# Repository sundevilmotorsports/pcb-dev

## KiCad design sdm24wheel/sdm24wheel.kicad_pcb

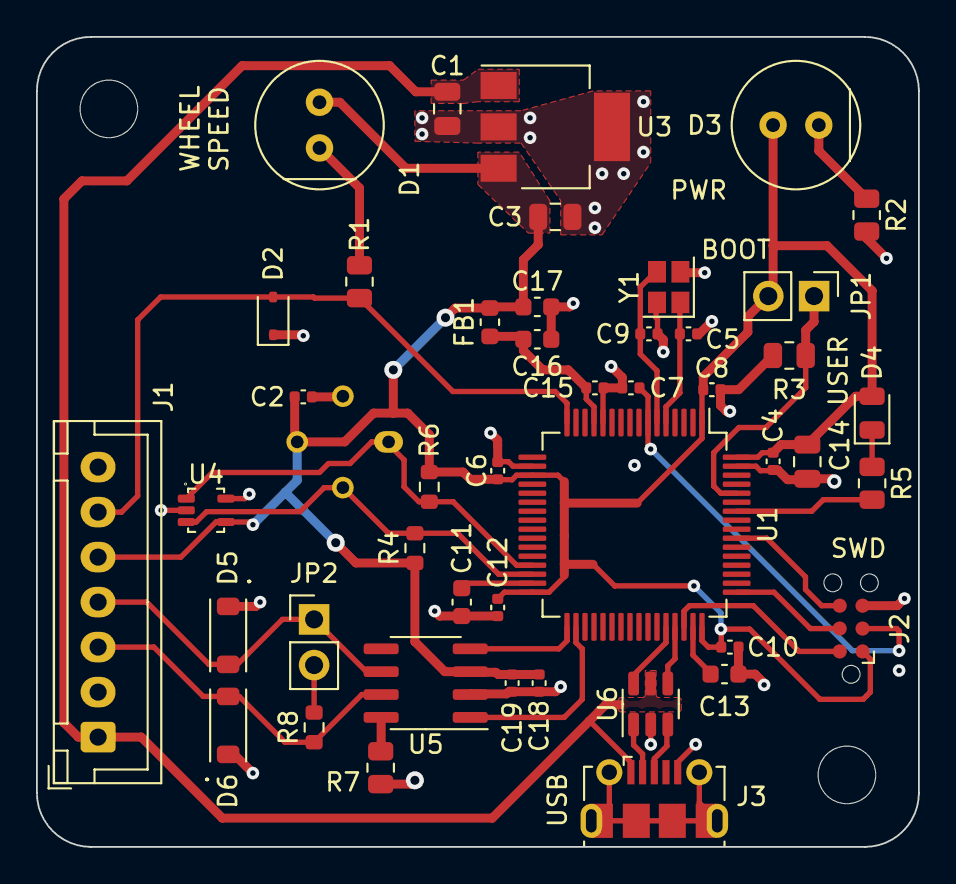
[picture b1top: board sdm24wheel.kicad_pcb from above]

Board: 4 copper layers, 49.0 x 45.0 mm, 48 parts (1 on the bottom side), 30 nets.

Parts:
C1, C3, C14: 10uF; C_0805_2012Metric
C2, C4, C6, C7, C8, C10, C12, C15, C18, C19: 100nF; C_0402_1005Metric
C5, C9: 10pF; C_0402_1005Metric
C11, C13: 2.2uF; C_0603_1608Metric
C16, C17: 1uF; C_0603_1608Metric
D1: GREEN; Dialight_561-XX0X-XXX
D2: TVS; D_SOD-323
D3: RED; Dialight_561-XX0X-XXX
D4: GREEN; LED_0805_2012Metric
D5, D6: TVS; SOD-123FL
FB1: 120R; L_0603_1608Metric
H1, H2: M3; MountingHole_3.2mm_M3
J1: JST-XH; JST_XH_B7B-XH-A_1x07_P2.50mm_Vertical
J2: Conn_ARM_SWD_TagConnect_TC2030; Tag-Connect_TC2030-IDC-NL_2x03_P1.27mm_Vertical
J3: USB_B_Micro; USB_Micro-B_Molex-105017-0001
JP1: BOOT; PinHeader_1x02_P2.54mm_Vertical
JP2: Bus Termination; PinHeader_1x02_P2.54mm_Vertical
R1, R2, R5: 220; R_0805_2012Metric
R3, R7: 10k; R_0805_2012Metric
R4, R6: 2.7k; R_0603_1608Metric
R8: 120; R_0603_1608Metric
U1: STM32F405RGT6; LQFP-64_10x10mm_P0.5mm
U2: MLX90614; TO-39-4
U3: MIC37100-3.3WS; SOT-223-3_TabPin2
U4: 24LC01BT-E/LT; SC-70-5
U5: SN65HVD230; SOIC-8_3.9x4.9mm_P1.27mm
U6: USBLC6-2SC6; SOT-23-6
Y1: 12MHz; Crystal_SMD_2520-4Pin_2.5x2.0mm

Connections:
+3.3V: C2.1, C3.1, C4.1, C6.1, C8.1, C10.1, C12.1, C14.1, C17.1, C18.1, C19.1, D1.2 (A), D3.2 (A), D4.2 (A), FB1.2, J1.5, J2.1 (VCC), JP1.2 (B), R4.1, R6.1, U1.1 (VBAT), U1.19 (VDD), U1.32 (VDD), U1.48 (VDD), U1.64 (VDD), U2.3 (VDD), U3.3 (OUT), U4.4 (Vcc), U5.3 (VCC)
+3.3VA: C15.1, C16.1, FB1.1, U1.13 (VDDA)
/BOOT0: JP1.1 (A), R3.2, U1.60 (BOOT0)
/CAN+: D6.2 (A2), J1.3, R8.1, U5.7 (CANH)
/CAN-: D5.2 (A2), J1.4, JP2.1 (A), U5.6 (CANL)
/CAN_Rs: R7.1, U5.8 (Rs)
/CRX: U1.33 (PB12), U5.4 (R)
/CTX: U1.34 (PB13), U5.1 (D)
/HE_LED: D1.1 (K), R1.2
/HE_OUTPUT: D2.2 (A2), J1.6, R1.1, U1.16 (PA2)
/HSE_IN: C5.1, U1.5 (PH0), Y1.1
/HSE_OUT: C9.1, U1.6 (PH1), Y1.3
/I2C2_SCL: R6.2, U1.29 (PB10), U2.1 (SCL), U4.1 (SCL)
/I2C2_SDA: R4.2, U1.30 (PB11), U2.2 (SDA), U4.3 (SDA)
/NRST: C7.1, J2.3 (~RESET), U1.7 (NRST)
/PWR_LED: D3.1 (K), R2.1
/SWCLK: J2.4 (SWCLK), U1.49 (PA14)
/SWDIO: J2.2 (SWDIO), U1.46 (PA13)
/SWO: J2.6 (SWO), U1.55 (PB3)
/USB_D+: U1.45 (PA12), U6.4 (I/O2)
/USB_D-: U1.44 (PA11), U6.6 (I/O1)
/USB_J_D+: J3.3 (D+), U6.3 (I/O2)
/USB_J_D-: J3.2 (D-), U6.1 (I/O1)
/USER_LED: R5.2, U1.58 (PB6)
/VCAP1: C11.1, U1.31 (VCAP_1)
/VCAP2: C13.1, U1.47 (VCAP_2)
GND: C1.2, C2.2, C3.2, C4.2, C5.2, C6.2, C7.2, C8.2, C9.2, C10.2, C11.2, C12.2, C13.2, C14.2, C15.2, C16.2, C17.2, C18.2, C19.2, D2.1 (A1), D5.1 (A1), D6.1 (A1), J1.2, J1.7, J2.5 (GND), J3.5 (GND), R2.2, R3.1, R7.2, U1.12 (VSSA), U1.18 (VSS), U1.63 (VSS), U2.4 (GND), U3.2 (GND), U4.2 (Vss), U4.5 (WP), U5.2 (GND), U6.2 (GND), Y1.2, Y1.4
unnamed: D4.1 (K), R5.1
unnamed: JP2.2 (B), R8.2
VCC: C1.1, J1.1, J3.1 (VBUS), U3.1 (IN), U6.5 (VBUS)

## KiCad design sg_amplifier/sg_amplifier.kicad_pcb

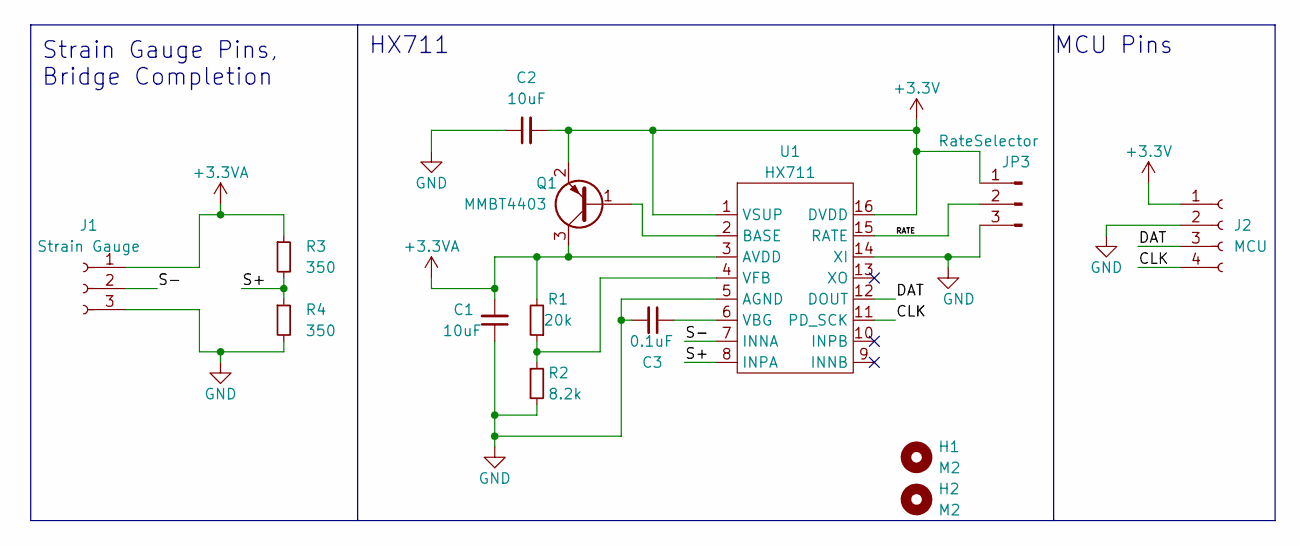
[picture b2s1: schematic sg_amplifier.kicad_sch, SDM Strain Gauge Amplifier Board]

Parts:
C1, C2: 10uF; C_0603_1608Metric
C3: 0.1uF; C_0402_1005Metric
H1, H2: M2; MountingHole_2.2mm_M2
J1: Strain Gauge; TerminalBlock_TE_282834-3_1x03_P2.54mm_Horizontal
J2: MCU; TerminalBlock_TE_282834-4_1x04_P2.54mm_Horizontal
JP3: RateSelector; PinHeader_1x03_P2.54mm_Vertical
Q1: MMBT4403; SOT-23
R1: 20k; R_0805_2012Metric
R2: 8.2k; R_0402_1005Metric
R3, R4: 350; R_Axial_DIN0414_L11.9mm_D4.5mm_P15.24mm_Horizontal
U1: HX711; SOP-16_3.9x9.9mm_P1.27mm

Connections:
+3.3V: C2.2, J2.1, JP3.1, Q1.2 (E), U1.1 (VSUP), U1.16 (DVDD)
+3.3VA: C1.2, J1.1, Q1.3 (C), R1.2, R3.1, U1.3 (AVDD)
/CLK: J2.4, U1.11 (PD_SCK)
/DAT: J2.3, U1.12 (DOUT)
/RATE: JP3.2, U1.15 (RATE)
/S+: R3.2, R4.1, U1.8 (INPA)
/S-: J1.2, U1.7 (INNA)
GND: C1.1, C2.1, C3.2, J1.3, J2.2, JP3.3, R2.2, R4.2, U1.5 (AGND), U1.14 (XI)
unnamed: C3.1, U1.6 (VBG)
unnamed: Q1.1 (B), U1.2 (BASE)
unnamed: R1.1, R2.1, U1.4 (VFB)

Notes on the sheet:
MCU Pins
Strain Gauge Pins, Bridge Completion
HX711

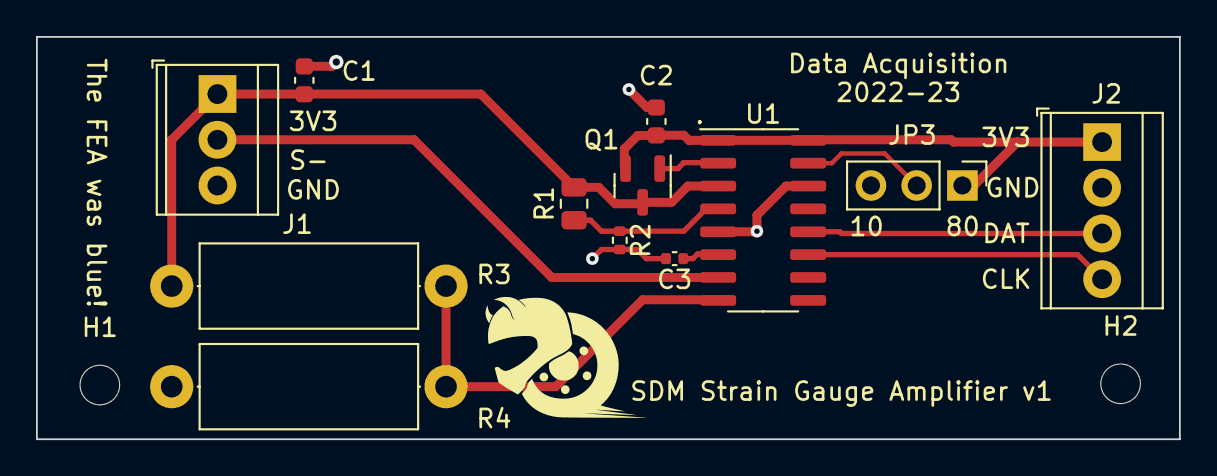
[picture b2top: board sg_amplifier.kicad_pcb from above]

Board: 2 copper layers, 63.5 x 22.4 mm, 14 parts (0 on the bottom side), 11 nets.

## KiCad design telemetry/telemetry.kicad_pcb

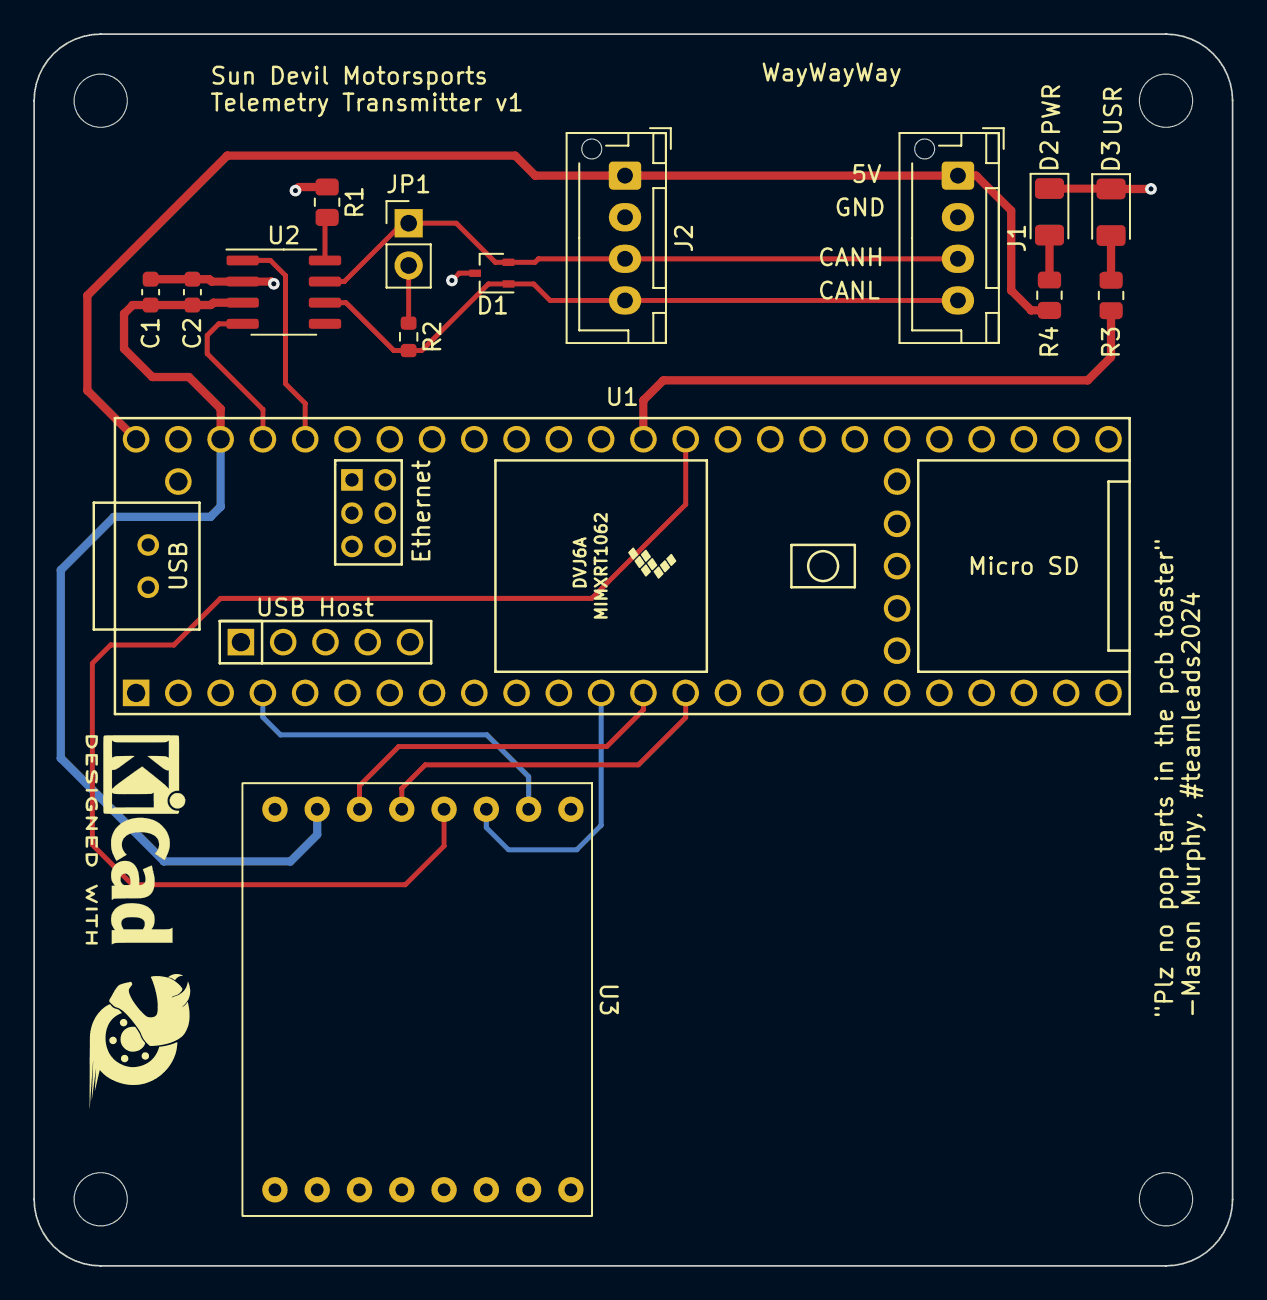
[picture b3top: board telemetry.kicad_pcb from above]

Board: 2 copper layers, 72.0 x 74.0 mm, 19 parts (0 on the bottom side), 17 nets.

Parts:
C1, C2: 100nF; C_0603_1608Metric
D1: ESDCAN; SOT-323_SC-70
D2: RED; LED_1206_3216Metric
D3: GREEN; LED_1206_3216Metric
H1, H2, H3, H4: M3; MountingHole_3.2mm_M3
J1: CAN; JST_XH_B4B-XH-AM_1x04_P2.50mm_Vertical
J2: CAN_DaisyChain; JST_XH_B4B-XH-AM_1x04_P2.50mm_Vertical
JP1: Bus Termination; PinHeader_1x02_P2.54mm_Vertical
R1: 10k; R_0805_2012Metric
R2: 120; R_0603_1608Metric
R3: 500; R_0805_2012Metric
R4: 220; R_0805_2012Metric
U1: Teensy4.1; Teensy41
U2: SN65HVD230; SOIC-8_3.9x4.9mm_P1.27mm
U3: nrf24L01-click

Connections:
+3.3V: C1.1, C2.1, U1.46 (3V3), U2.3 (VCC), U3.7 (3V3)
+5V: J1.1, J2.1, R4.1, U1.48 (VIN)
/CANH: D1.2 (A2), J1.3, J2.3, JP1.1 (A), U2.7 (CANH)
/CANL: D1.1 (A1), J1.4, J2.4, R2.2, U2.6 (CANL)
/CAN_Rs: R1.2, U2.8 (Rs)
/CE: U1.4 (2_OUT2), U3.2 (CE)
/CRX1: U1.45 (23_A9_CRX1_MCLK1), U2.4 (R)
/CS: U1.12 (10_CS_MQSR), U3.3 (CS)
/CTX1: U1.44 (22_A8_CTX1), U2.1 (D)
/MISO: U1.14 (12_MISO_MQSL), U3.5 (SDO)
/MOSI: U1.13 (11_MOSI_CTX1), U3.6 (SDI)
/PWR_LED: D2.2 (A), R4.2
/SCK: U1.35 (13_SCK_LED), U3.4 (SCK)
/USER_LED: R3.1, U1.36 (14_A0_TX3_SPDIF_OUT)
/USR_LED_RSTR: D3.2 (A), R3.2
GND: C1.2, C2.2, D1.3 (common), D2.1 (K), D3.1 (K), J1.2, J2.2, R1.1, U1.1 (GND), U1.34 (GND), U1.47 (GND), U2.2 (GND), U3.8 (GND), U3.9 (GND)
unnamed: JP1.2 (B), R2.1

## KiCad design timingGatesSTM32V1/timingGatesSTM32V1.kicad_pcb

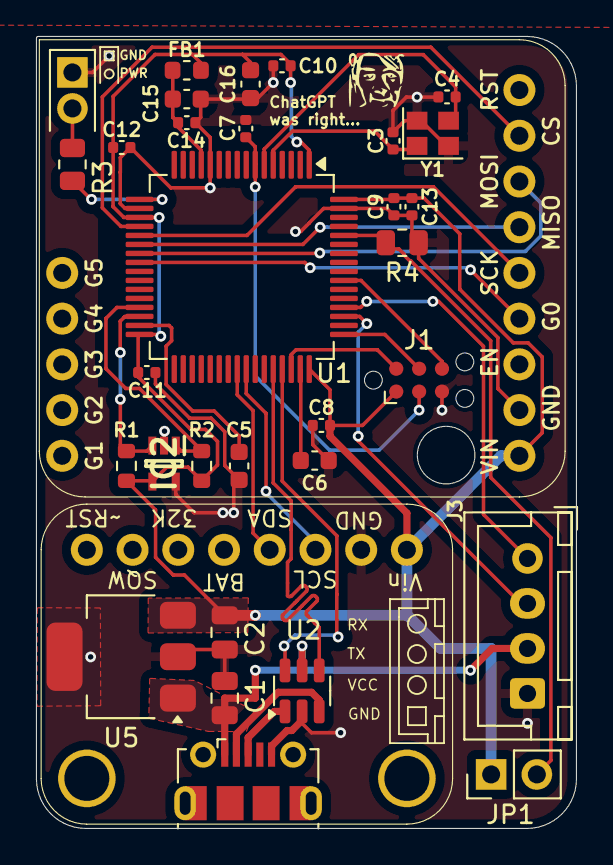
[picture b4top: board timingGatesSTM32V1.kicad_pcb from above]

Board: 4 copper layers, 30.0 x 44.0 mm, 34 parts (0 on the bottom side), 30 nets.

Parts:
C1, C2: 10uF; C_0805_2012Metric
C3, C4: 10pF; C_0402_1005Metric
C5, C6: 2.2uF; C_0603_1608Metric
C7, C8, C9, C10, C11, C12, C13, C14: 100nF; C_0402_1005Metric
C15, C16: 1uF; C_0603_1608Metric
D1: RED (floating); LED_0805_2012Metric
FB1: 120R; L_0603_1608Metric
H1: M3; MountingHole_3.2mm_M3
IC2: 24LC01BT-E_LT; SOT65P210X110-5N
J1: Conn_ARM_SWD_TagConnect_TC2030; Tag-Connect_TC2030-IDC-NL_2x03_P1.27mm_Vertical
J2: USB_B_Micro; USB_Micro-B_Molex-105017-0001
J3: Conn_01x04_Socket; JST_XH_B4B-XH-A_1x04_P2.50mm_Vertical
JP1: BOOT; PinHeader_1x02_P2.54mm_Vertical
R1, R2: 2.7k; R_0603_1608Metric
R3: 220; R_0805_2012Metric
R4: 10k; R_0805_2012Metric
U1: STM32F405RGT6; LQFP-64_10x10mm_P0.5mm
U2: USBLC6-2SC6; SOT-23-6
U3: RFM95W
U4: DS3231
U5: MIC37100-3.3WS; SOT-223-3_TabPin2
Y1: 12MHz; Crystal_SMD_2520-4Pin_2.5x2.0mm

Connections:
+3.3V: C2.1, C8.2, C9.2, C10.2, C11.2, C12.2, C13.2, C16.2, FB1.2, IC2.4 (VCC), J1.1 (VCC), JP1.1 (A), R1.2, R2.2, U1.1 (VBAT), U1.19 (VDD), U1.32 (VDD), U1.48 (VDD), U1.64 (VDD), U3.1 (Vin), U4.1 (Vin), U5.3 (OUT)
/BOOT0: JP1.2 (B), R4.2, U1.60 (BOOT0)
/G0: U1.24 (PC4), U3.4 (G0)
/HSE_IN: C3.1, U1.5 (PH0), Y1.1
/HSE_OUT: C4.1, U1.6 (PH1), Y1.3
/I2C2_SCL: IC2.1 (SCL), R2.1, U1.29 (PB10)
/I2C2_SDA: IC2.3 (SDA), R1.1, U1.30 (PB11)
/I2C3_SCL: U1.41 (PA8), U4.3 (SCL)
/I2C3_SDA: U1.40 (PC9), U4.4 (SDA)
/NRST: C7.2, J1.3 (~RESET), U1.7 (NRST)
/SPI1_MISO: U1.22 (PA6), U3.6 (MISO)
/SPI1_MOSI: U1.23 (PA7), U3.7 (MOSI)
/SPI1_NSS: U1.20 (PA4), U3.8 (CS)
/SPI1_SCK: U1.21 (PA5), U3.5 (SCK)
/SWCLK: J1.4 (SWCLK), U1.49 (PA14)
/SWDIO: J1.2 (SWDIO), U1.46 (PA13)
/SWO: J1.6 (SWO), U1.55 (PB3)
/USART3_RX: J3.1, U1.52 (PC11)
/USART3_TX: J3.2, U1.51 (PC10)
/USB_D+: U1.45 (PA12), U2.6 (I/O1)
/USB_D-: U1.44 (PA11), U2.4 (I/O2)
/VCAP_1: C5.1, U1.31 (VCAP_1)
/VCAP_2: C6.2, U1.47 (VCAP_2)
GND: C1.2, C2.2, C3.2, C4.2, C5.2, C6.1, C7.1, C8.1, C9.1, C10.1, C11.1, C12.1, C13.1, C14.1, C15.1, C16.1, D1.1 (K), IC2.2 (Vss), IC2.5 (WP), J1.5 (GND), J2.5 (GND), J3.4, R4.1, U1.12 (VSSA), U1.18 (VSS), U1.63 (VSS), U2.2 (GND), U3.2 (GND), U4.2 (GND), U5.2 (GND), Y1.2, Y1.4
unnamed: D1.2 (A), R3.1
unnamed: J2.3 (D+), U2.1 (I/O1)
unnamed: J2.2 (D-), U2.3 (I/O2)
unnamed: R3.2, U1.17 (PA3)
unnamed: C14.2, C15.2, FB1.1, U1.13 (VDDA)
VCC: C1.1, J2.1 (VBUS), J3.3, U2.5 (VBUS), U5.1 (IN)

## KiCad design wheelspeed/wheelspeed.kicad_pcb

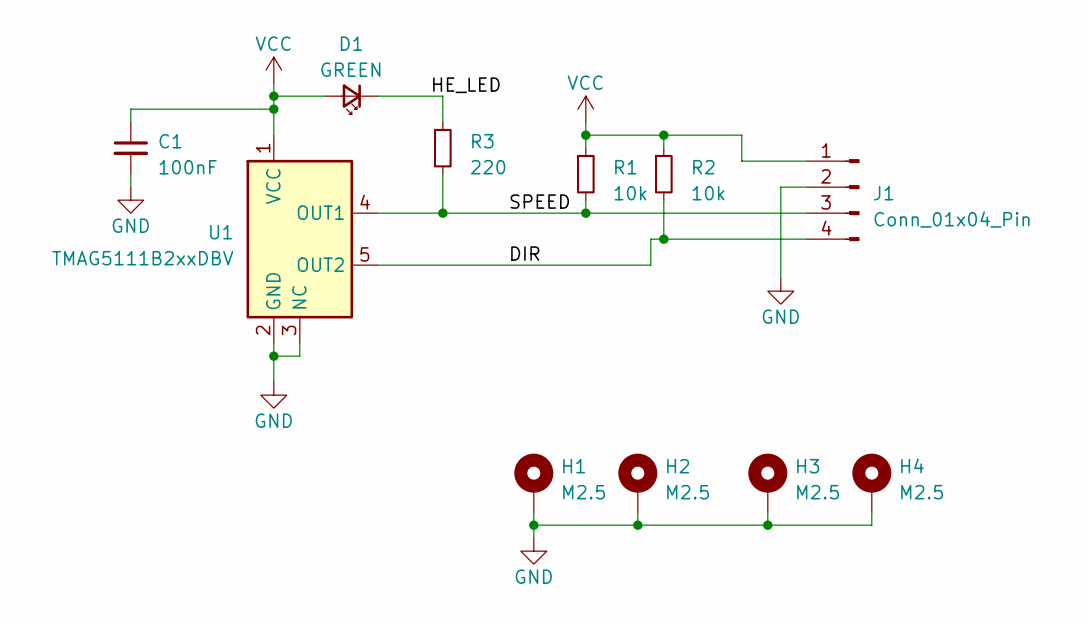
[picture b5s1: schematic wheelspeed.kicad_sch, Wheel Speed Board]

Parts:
C1: 100nF; C_0603_1608Metric
D1: GREEN; LED_1206_3216Metric
H1, H2, H3, H4: M2.5; MountingHole_2.7mm_M2.5_ISO7380_Pad
J1: Conn_01x04_Pin; JST_XH_B4B-XH-AM_1x04_P2.50mm_Vertical
R1, R2: 10k; R_0805_2012Metric
R3: 220; R_0805_2012Metric
U1: TMAG5111B2xxDBV; SOT-23-5

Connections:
/DIR: J1.4, R2.2, U1.5 (OUT2)
/HE_LED: D1.1 (K), R3.1
/SPEED: J1.3, R1.2, R3.2, U1.4 (OUT1)
GND: C1.2, H1.1, H2.1, H3.1, H4.1, J1.2, U1.2 (GND), U1.3 (NC)
VCC: C1.1, D1.2 (A), J1.1, R1.1, R2.1, U1.1 (VCC)

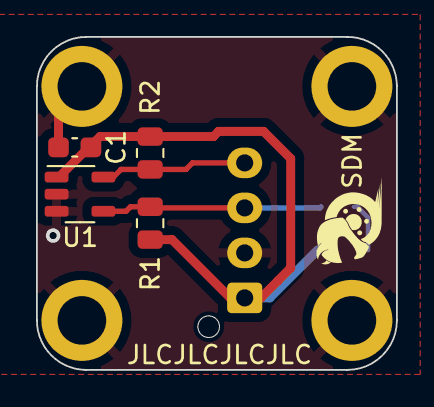
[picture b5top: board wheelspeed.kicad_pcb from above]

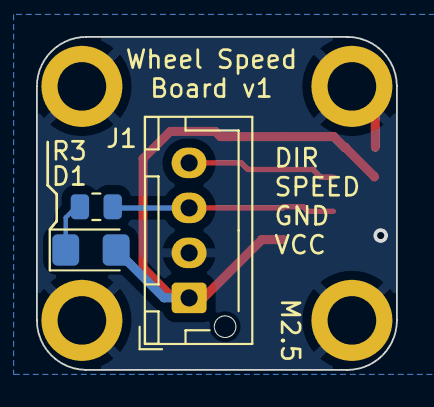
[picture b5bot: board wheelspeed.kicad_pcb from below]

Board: 2 copper layers, 20.0 x 18.5 mm, 11 parts (3 on the bottom side), 5 nets.

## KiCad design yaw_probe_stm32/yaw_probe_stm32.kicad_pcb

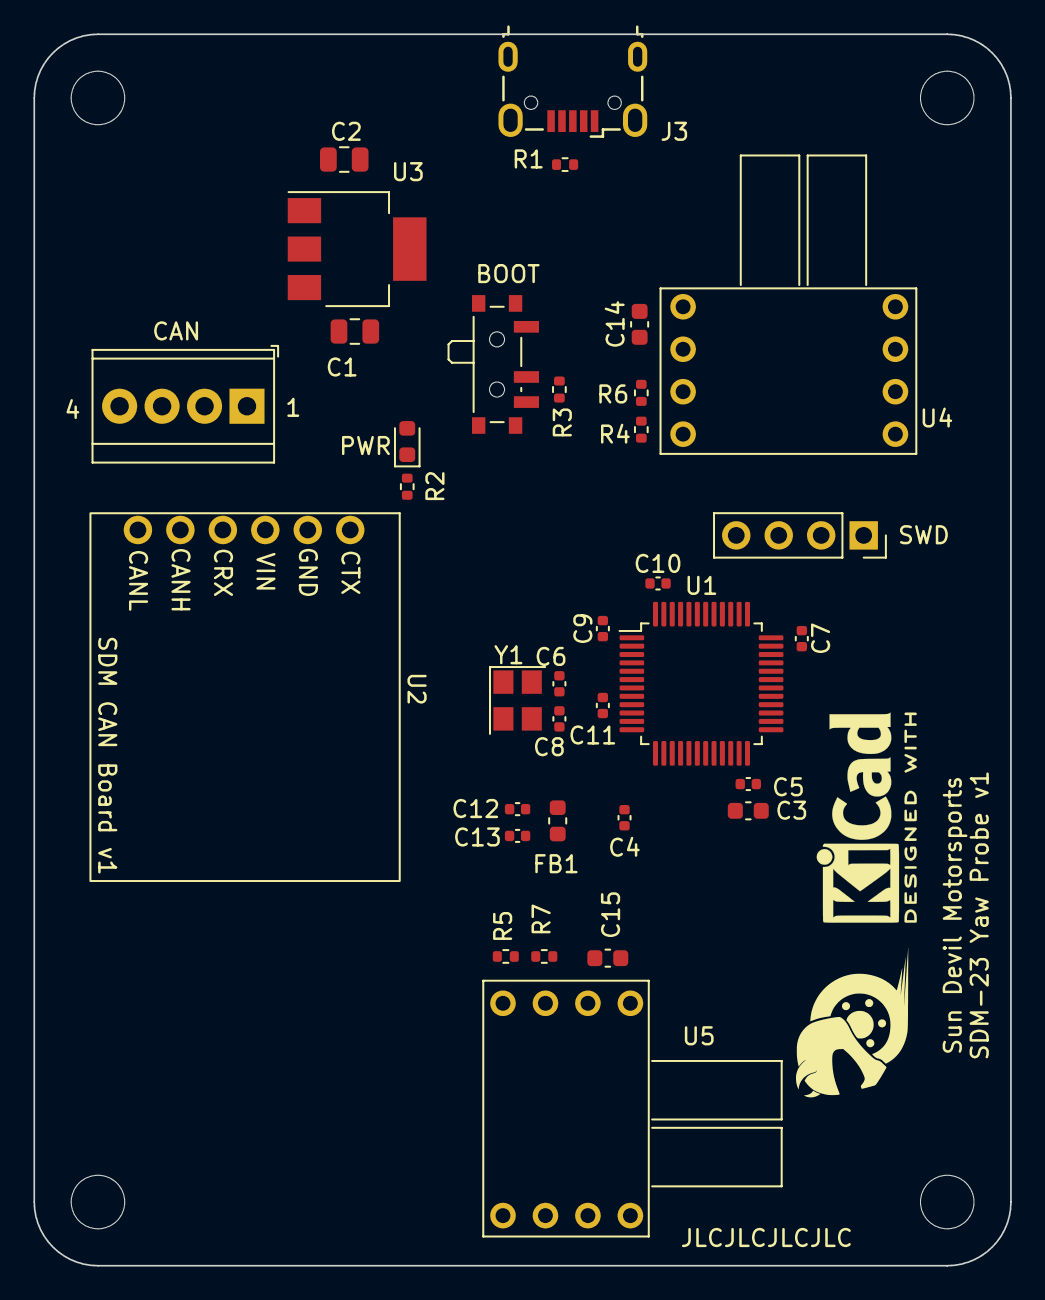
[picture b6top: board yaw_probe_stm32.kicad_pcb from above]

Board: 2 copper layers, 58.4 x 73.7 mm, 38 parts (0 on the bottom side), 22 nets, no tracks yet.

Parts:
C1, C2: 22uF; C_0805_2012Metric
C3: 10uF; C_0603_1608Metric
C4, C5, C7, C9, C10: 100nF; C_0402_1005Metric
C6, C8: 10pF; C_0402_1005Metric
C11: 10nF; C_0402_1005Metric
C12, C13: 1uF; C_0402_1005Metric
C14, C15: 0.1uF; C_0603_1608Metric
D1: GREEN; LED_0603_1608Metric
FB1: 120R; L_0603_1608Metric
H1, H2, H3, H4: M3; MountingHole_3.2mm_M3
J1: CONN_CAN; TerminalBlock_TE_282834-4_1x04_P2.54mm_Horizontal
J2: Conn_01x04_Male; PinSocket_1x04_P2.54mm_Vertical
J3: USB_B_Micro; USB_Micro-B_Wuerth_629105150521
R1, R2: 1k5; R_0402_1005Metric
R3: 10k; R_0402_1005Metric
R4, R5, R6, R7: 4k7; R_0402_1005Metric
SW1: SW_SPDT; SW_SPDT_PCM12
U1: STM32F072C8Tx; LQFP-48_7x7mm_P0.5mm
U2: SN65HVD230_CAN_Transceiver; SDM_CANBoard_v1
U3: AMS1117-3.3; SOT-223-3_TabPin2
U4, U5: MS4525DO; MS4525-DSvoxxxyP
Y1: 16MHz; Crystal_SMD_3225-4Pin_3.2x2.5mm

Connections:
+3.3V: C2.1, C3.1, C5.1, C7.1, C9.1, C10.1, C13.1, C14.1, C15.1, D1.2 (A), FB1.1, J2.1, R1.1, R4.1, R5.1, R6.1, R7.1, SW1.3 (C), U1.1 (VBAT), U1.24 (VDD), U1.36 (VDDIO2), U1.48 (VDD), U2.3 (3V3), U3.2 (VO), U4.2 (VCC), U5.2 (VCC)
+3.3VA: C11.1, C12.1, FB1.2, U1.9 (VDDA)
/BOOT0: R3.2, U1.44 (BOOT0)
/CANH: J1.2, U2.5 (CANH)
/CANL: J1.3, U2.6 (CANL)
/CAN_RX: U1.45 (PB8), U2.4 (CRX)
/CAN_TX: U1.46 (PB9), U2.1 (CTX)
/I2C1_SCL: R4.2, U1.42 (PB6), U4.4 (SCL)
/I2C1_SDA: R6.2, U1.43 (PB7), U4.3 (SDA)
/I2C2_SCL: R5.2, U1.21 (PB10), U5.4 (SCL)
/I2C2_SDA: R7.2, U1.22 (PB11), U5.3 (SDA)
/NRST: C4.1, U1.7 (NRST)
/OSC_IN: C6.1, U1.5 (PF0), Y1.1
/OSC_OUT: C8.1, U1.6 (PF1), Y1.3
/PWR_LED: D1.1 (K), R2.1
/SWCLK: J2.3, U1.37 (PA14)
/SWDIO: J2.2, U1.34 (PA13)
/SW_BOOT0: R3.1, SW1.2 (B)
/USB_D+: J3.3 (D+), R1.2, U1.33 (PA12)
/USB_D-: J3.2 (D-), U1.32 (PA11)
GND: C1.2, C2.2, C3.2, C4.2, C5.2, C6.2, C7.2, C8.2, C9.2, C10.2, C11.2, C12.2, C13.2, C14.2, C15.2, J1.4, J2.4, J3.5 (GND), R2.2, SW1.1 (A), U1.8 (VSSA), U1.23 (VSS), U1.35 (VSS), U1.47 (VSS), U2.2 (GND), U3.1 (GND), U4.1 (GND), U5.1 (GND), Y1.2, Y1.4
VBUS: C1.1, J1.1, J3.1 (VBUS), U3.3 (VI)
